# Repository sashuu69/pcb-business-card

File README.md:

# PCB Business Card

## Introduction

My personal PCB business card

## Design

### Front

### Bottom

### Drills

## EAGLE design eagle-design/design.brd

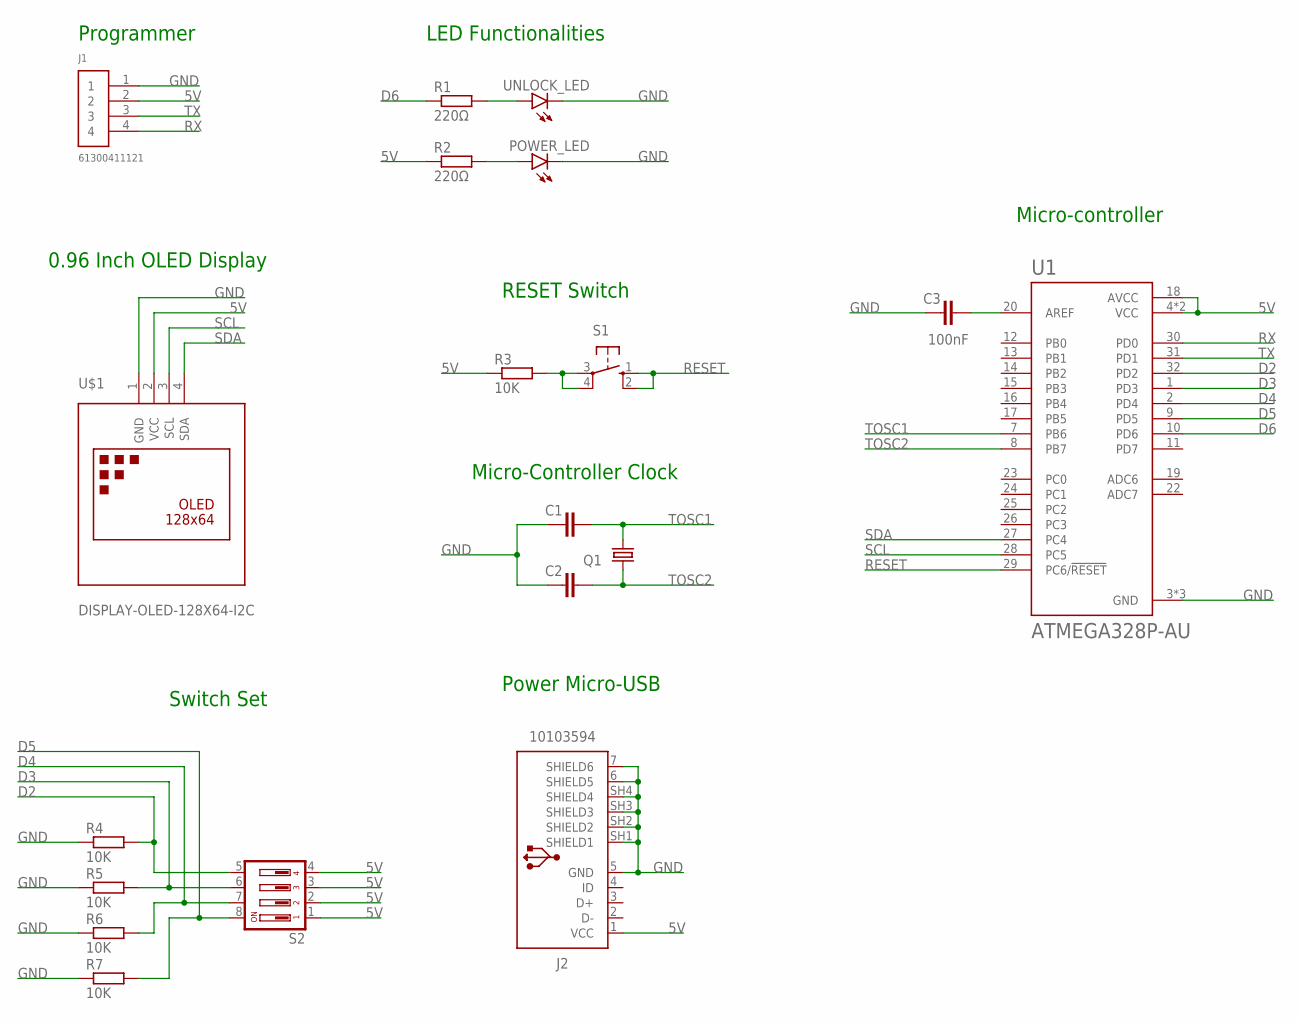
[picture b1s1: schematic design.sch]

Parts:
C1, C2: C-EUC0805; C0805
C3: 100nF; C0805
J1: 61300411121
J2: 10103594
POWER_LED: LEDCHIP-LED0805; CHIP-LED0805
Q1: CRYSTALHC49U-V; HC49U-V
R1, R2: 220Ω; R0805
R3, R4, R5, R6, R7: 10K; R0805
S1: 10-XX; B3F-10XX
S2: DA04; DA-04
U1: ATMEGA328P-AU; QFP80P900X900X120-32N
U$1: DISPLAY-OLED-128X64-I2C
UNLOCK_LED: LEDCHIP-LED0805; CHIP-LED0805

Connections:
5V: J1.2, J2.1 (VCC), R2.1, R3.1, S2.1, S2.2, S2.3, S2.4, U1.4 (VCC), U1.6 (VCC), U1.18 (AVCC), U$1.2 (VCC)
D2: R4.2, S2.5, U1.32 (PD2)
D3: R5.2, S2.6, U1.1 (PD3)
D4: R6.2, S2.7, U1.2 (PD4)
D5: R7.2, S2.8, U1.9 (PD5)
D6: R1.1, U1.10 (PD6)
GND: C1.1, C2.1, C3.1, J1.1, J2.5 (GND), J2.6 (SHIELD5), J2.7 (SHIELD6), J2.SH1 (SHIELD1), J2.SH2 (SHIELD2), J2.SH3 (SHIELD3), J2.SH4 (SHIELD4), POWER_LED.C, R4.1, R5.1, R6.1, R7.1, U1.3 (GND), U1.5 (GND), U1.21 (GND), U$1.1 (GND), UNLOCK_LED.C
unnamed: R1.2, UNLOCK_LED.A
unnamed: R3.2, S1.3, S1.4 (P1)
unnamed: POWER_LED.A, R2.2
unnamed: C3.2, U1.20 (AREF)
RESET: S1.1 (S), S1.2 (S1), U1.29 (PC6/!RESET)
RX: J1.4, U1.30 (PD0)
SCL: U1.28 (PC5), U$1.3 (SCL)
SDA: U1.27 (PC4), U$1.4 (SDA)
TOSC1: C1.2, Q1.2, U1.7 (PB6)
TOSC2: C2.2, Q1.1, U1.8 (PB7)
TX: J1.3, U1.31 (PD1)

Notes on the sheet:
Programmer
Power Micro-USB
0.96 Inch OLED Display
LED Functionalities
RESET Switch
Micro-Controller Clock
Switch Set
Micro-controller

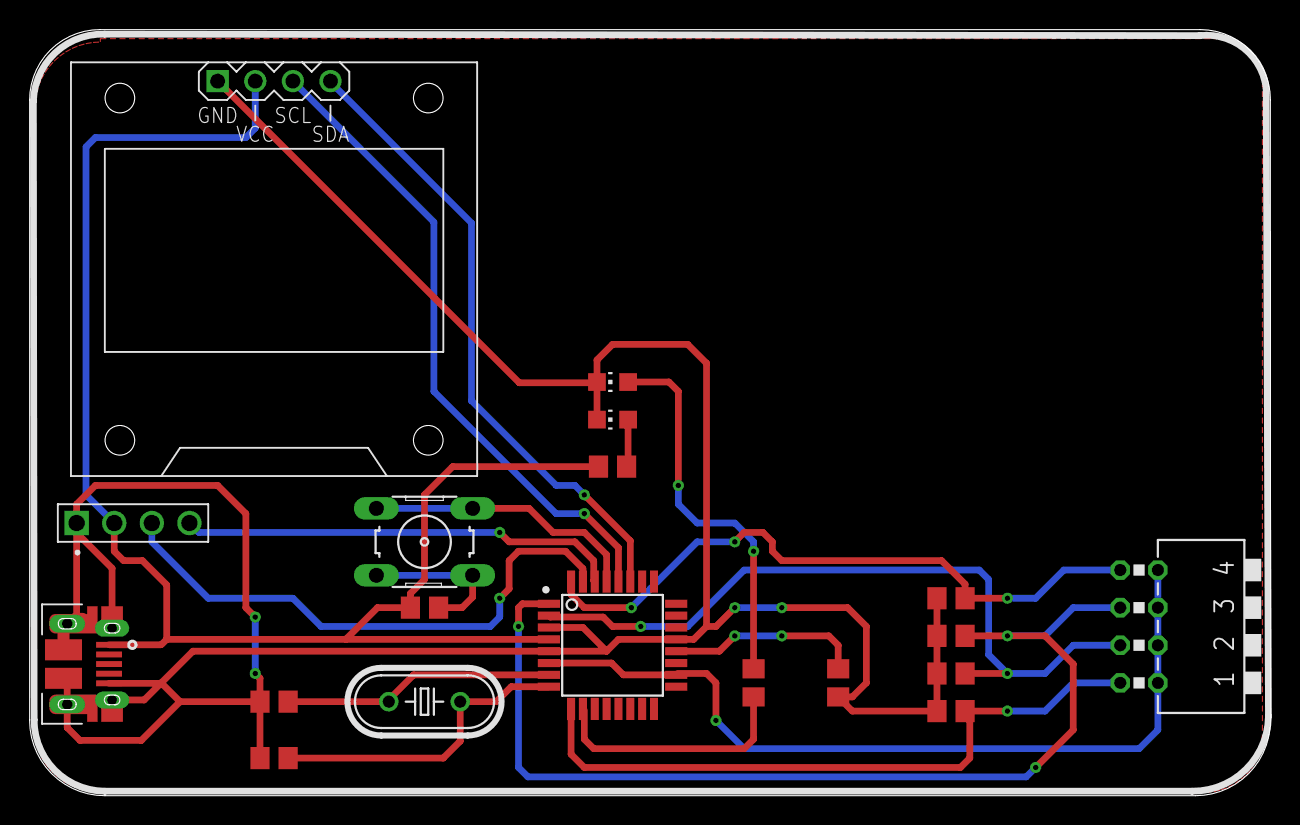
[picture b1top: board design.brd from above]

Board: 2 copper layers, 83.8 x 51.7 mm, 19 parts (0 on the bottom side), 18 nets.

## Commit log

2021-07-17 Added .gitignore
2021-07-17 Added eagle-design data
2021-07-18 version 1 schematics complete
2021-07-18 Simple reorg
2021-07-18 Created brd
2021-07-18 Added export files
2021-07-18 Added image exports
2021-07-19 Small change
2021-07-24 Updated design and export files
2021-07-28 Added GND plane for bottom layer
2021-07-28 Removed unnecessary files
2021-07-28 Updated exports
2021-07-29 Added ratsnet to top and bottom layer
2021-07-29 Exported latest docs
2021-07-29 fixing rough edges
2021-07-29 New exports
2021-07-29 Fixed errors
2022-05-03 Added PCB photos
2024-06-30 feat: text change

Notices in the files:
parts and their libraries:
diy-modules: Released under the Creative Commons Attribution 4.0 International License: http://creativecommons.org/licenses/by/4.0
